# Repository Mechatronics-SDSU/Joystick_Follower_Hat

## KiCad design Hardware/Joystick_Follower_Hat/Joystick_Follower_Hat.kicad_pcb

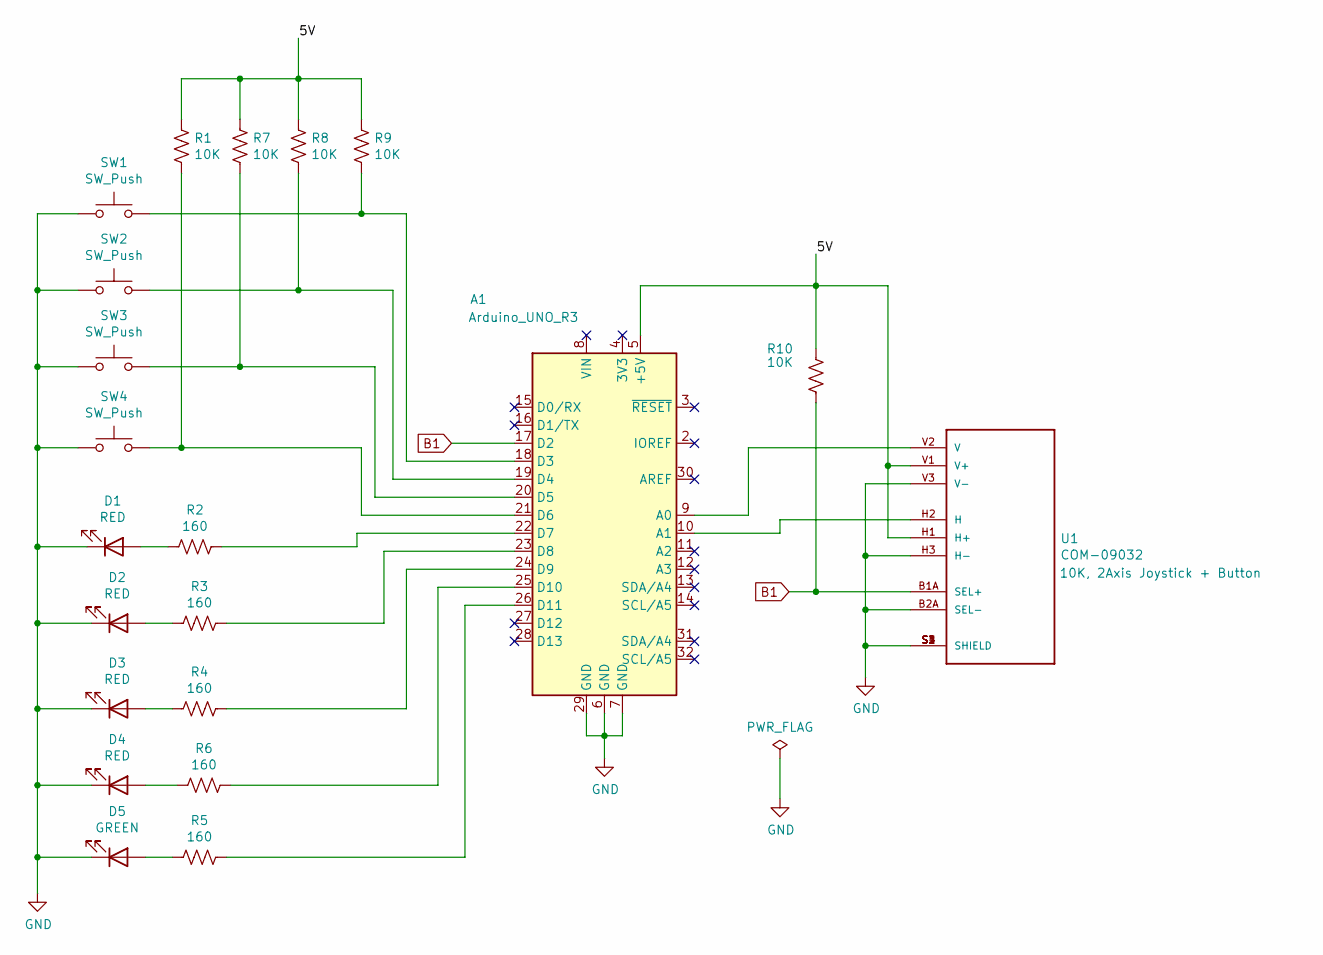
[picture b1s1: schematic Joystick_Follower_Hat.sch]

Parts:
A1: Arduino_UNO_R3
D1, D2, D3, D4: RED; LED_D5.0mm
D5: GREEN; LED_D5.0mm
R1, R7, R8, R9, R10: 10K; R_Axial_DIN0207_L6.3mm_D2.5mm_P10.16mm_Horizontal
R2, R3, R4, R5, R6: 160; R_Axial_DIN0207_L6.3mm_D2.5mm_P10.16mm_Horizontal
SW1, SW2, SW3, SW4: SW_Push; SW_PUSH-12mm
U1: COM-09032; XDCR_COM-09032

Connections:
/5V: A1.5 (+5V), R1.1, R7.1, R8.1, R9.1, R10.2, U1.H1 (H+), U1.V1 (V+)
B1: A1.17 (D2), R10.1, U1.B1A (SEL+)
GND: A1.6 (GND), A1.7 (GND), A1.29 (GND), D1.1 (K), D2.1 (K), D3.1 (K), D4.1 (K), D5.1 (K), SW1.1, SW2.1, SW3.1, SW4.1, U1.B2A (SEL-), U1.H3 (H-), U1.S1 (SHIELD), U1.S2 (SHIELD), U1.S3 (SHIELD), U1.S4 (SHIELD), U1.V3 (V-)
unnamed: A1.9 (A0), U1.V2 (V)
unnamed: A1.10 (A1), U1.H2 (H)
unnamed: A1.18 (D3), R9.2, SW1.2
unnamed: A1.19 (D4), R8.2, SW2.2
unnamed: A1.20 (D5), R7.2, SW3.2
unnamed: A1.21 (D6), R1.2, SW4.2
unnamed: A1.22 (D7), R2.1
unnamed: A1.23 (D8), R3.1
unnamed: A1.24 (D9), R4.1
unnamed: A1.25 (D10), R6.1
unnamed: A1.26 (D11), R5.1
unnamed: D1.2 (A), R2.2
unnamed: D2.2 (A), R3.2
unnamed: D3.2 (A), R4.2
unnamed: D4.2 (A), R6.2
unnamed: D5.2 (A), R5.2

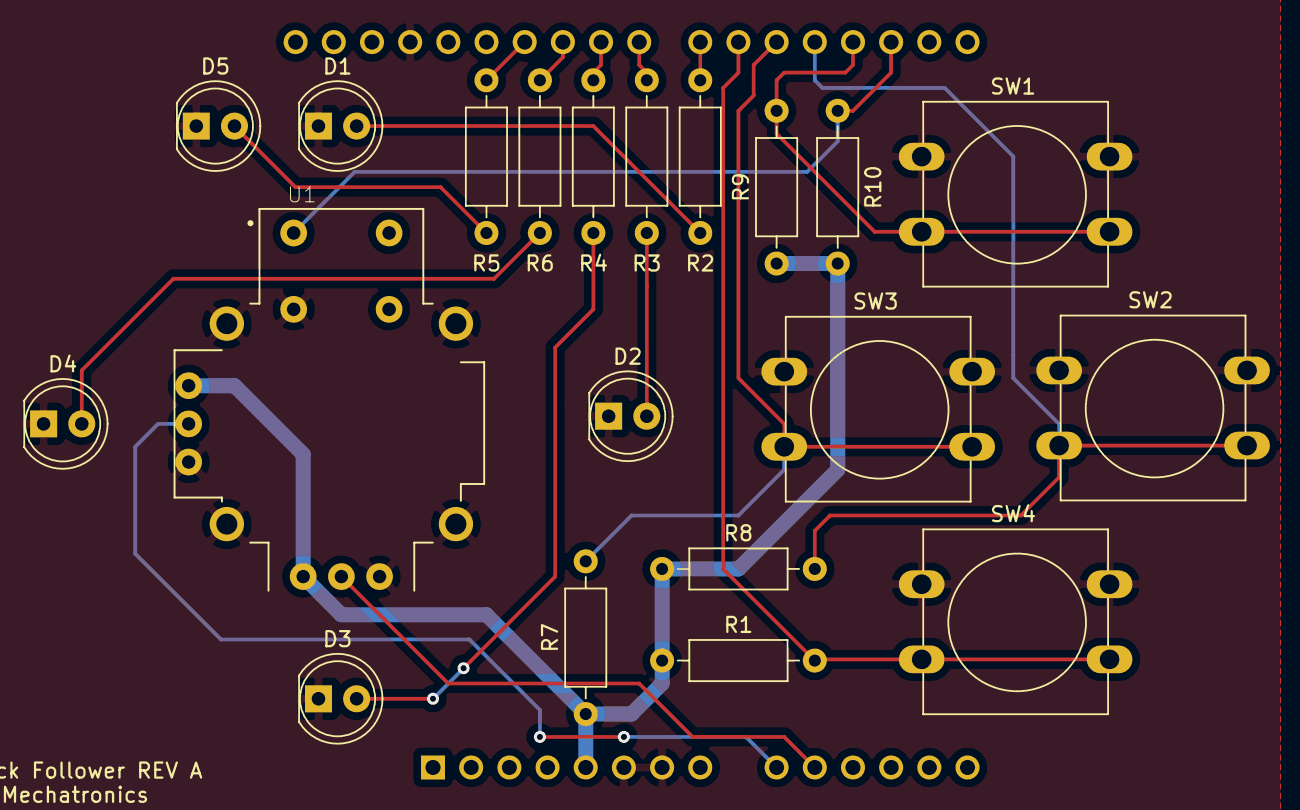
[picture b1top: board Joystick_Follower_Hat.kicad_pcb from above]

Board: 2 copper layers, 21 parts (1 on the bottom side), 19 nets.

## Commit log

2020-10-06 KiCad schematic of Joystick Follower.
2020-10-10 PCB Files and Gerber Files
2020-10-24 PCB name change
2020-10-24 sUpdated Gerbers
2020-12-23 Wrote code for the Arudino to control the LED's using the joystick.
